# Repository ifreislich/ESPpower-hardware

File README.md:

# ESPpower-hardware

Hardware for reading EKM Omnimeters.

The barrel jack is center positive.

The RJ-12 connection
Pin|Signal
---|------
1|GND
2|RS485-B
3|RS485-A
4|GND
5|n.c.
6|n.c.

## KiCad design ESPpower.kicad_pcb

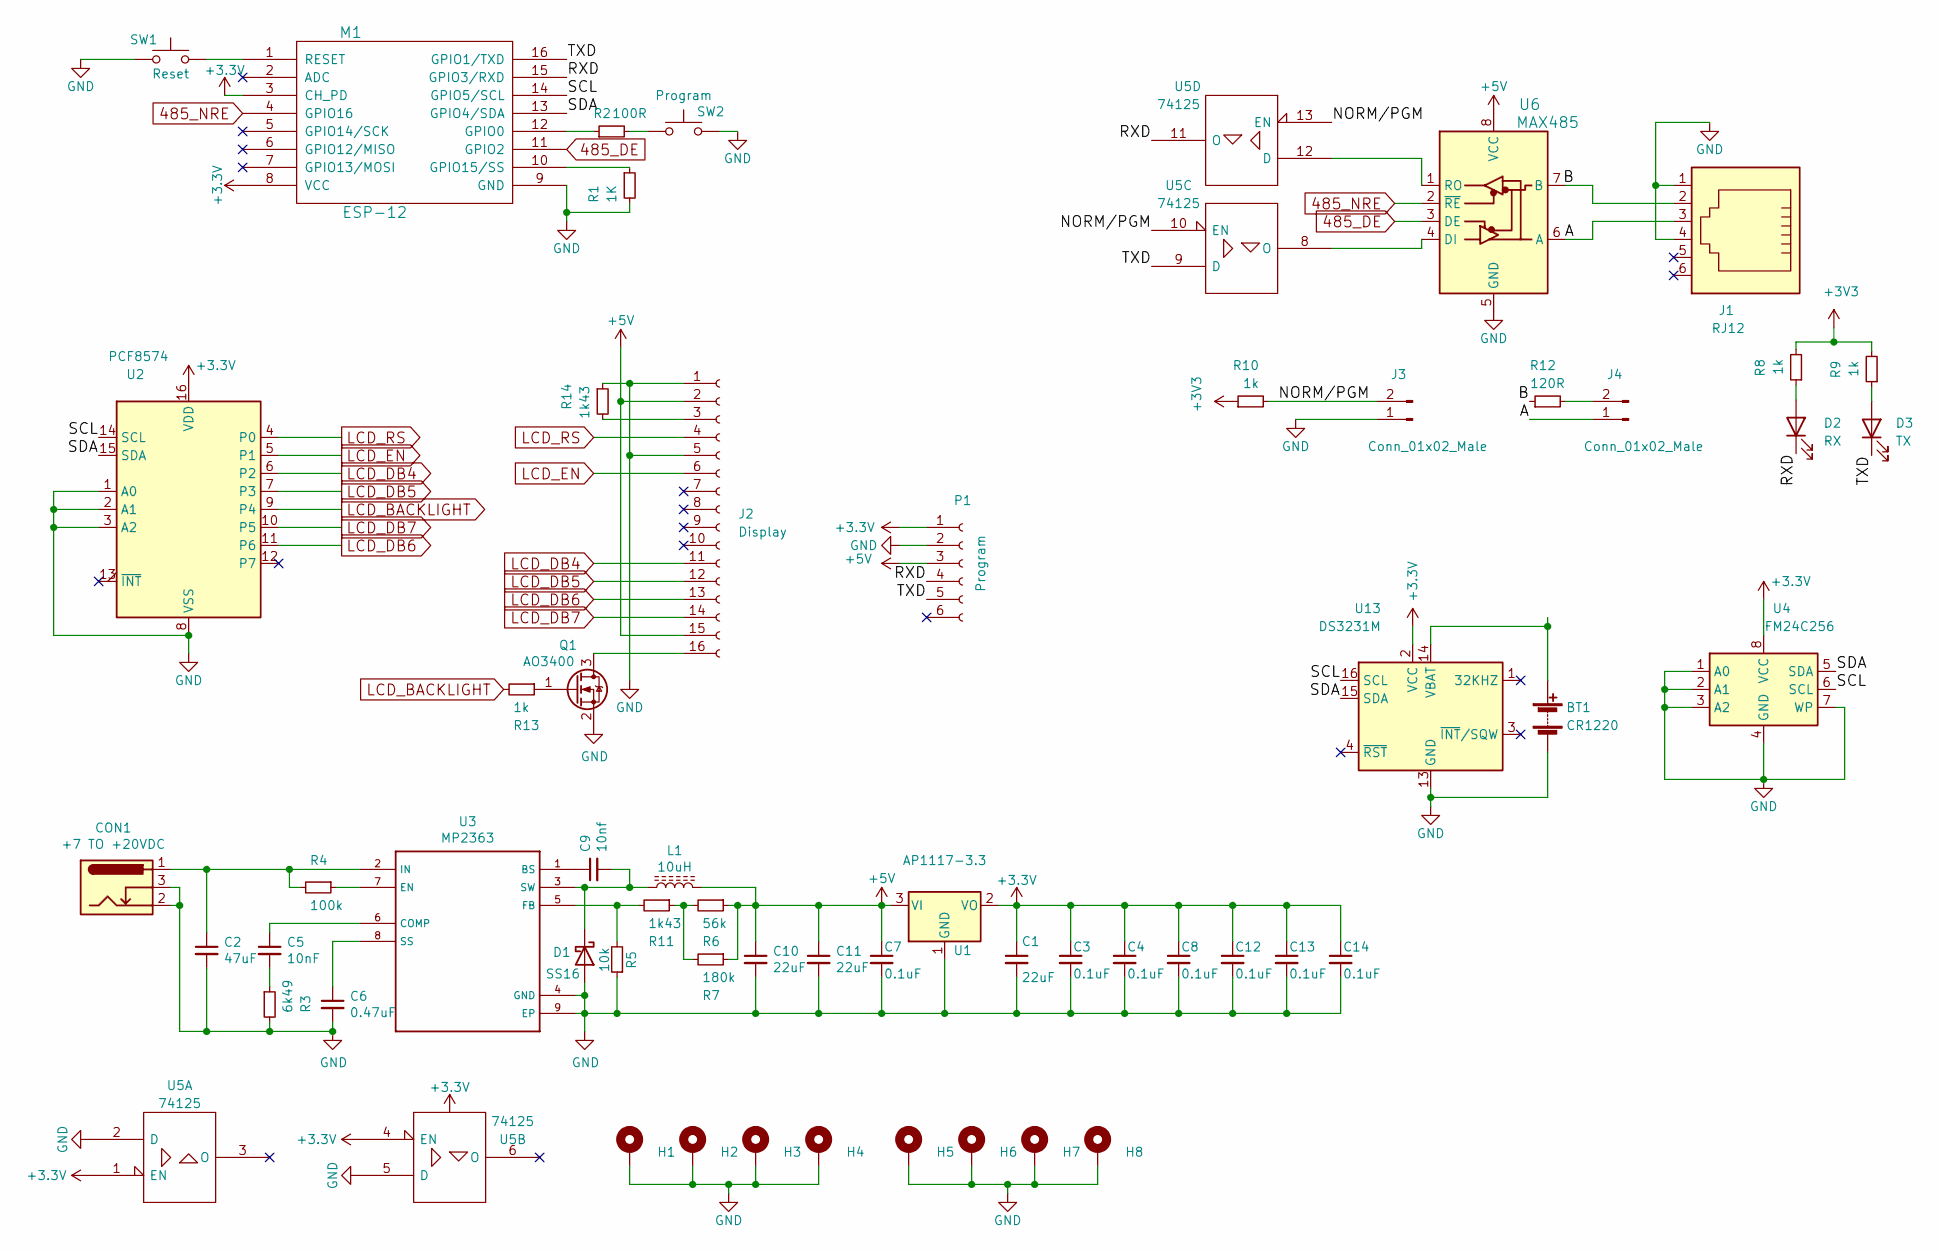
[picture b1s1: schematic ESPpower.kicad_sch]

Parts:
BT1: CR1220; CR1220SMD
C1: 22uF; C_1206_3216Metric
C2: 47uF; C_1206_3216Metric
C3, C4, C7, C8, C12, C13, C14: 0.1uF; C_0603_1608Metric
C5: 10nF; C_0805_2012Metric
C6: 0.47uF; C_0805_2012Metric
C9: 10nf; C_0805_2012Metric
C10, C11: 22uF; C_0805_2012Metric
CON1: +7 TO +20VDC; BarrelJack_Horizontal
D1: SS16; D_SMA
D2: RX; LED_0603_1608Metric
D3: TX; LED_0603_1608Metric
H1, H2, H3, H4, H5, H6, H7, H8: MountingHole_Pad; MountingHole_2.5mm_Pad_Via
J1: RJ12; RJ12_Amphenol_54601
J2: Display; PinSocket_1x16_P2.54mm_Vertical
J3, J4: Conn_01x02_Male; PinHeader_1x02_P2.54mm_Vertical
L1: 10uH; L_7.3x7.3_H3.5
M1: ESP-12; ESP-07
P1: Program; Pin_Header_Straight_1x06
Q1: AO3400; SOT-23
R1: 1K; R_0603_1608Metric
R2: 100R; R_0603_1608Metric
R3: 6k49; R_0603_1608Metric
R4: 100k; R_0603_1608Metric
R5: 10k; R_0603_1608Metric
R6: 56k; R_0805_2012Metric
R7: 180k; R_0805_2012Metric
R8, R9, R10, R13: 1k; R_0603_1608Metric
R11: 1k43; R_0805_2012Metric
R12: 120R; R_1206_3216Metric
R14: 1k43; R_0603_1608Metric
SW1: Reset; SW_PUSH_6mm
SW2: Program; SW_PUSH_6mm
U1: AP1117-3.3; SOT-223-3_TabPin2
U2: PCF8574; SOIC-16W_7.5x10.3mm_P1.27mm
U3: MP2363; HSOP-8-1EP_3.9x4.9mm_P1.27mm_EP2.41x3.1mm_ThermalVias
U4: FM24C256; SOIC-8_5.23x5.23mm_P1.27mm
U5: 74125; SOIC-14_3.9x8.7mm_P1.27mm
U6: MAX485; SOIC-8_3.9x4.9mm_P1.27mm
U13: DS3231M; SOIC-16W_7.5x10.3mm_P1.27mm

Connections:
485_DE: M1.11 (GPIO2), U6.3 (DE)
485_NRE: M1.4 (GPIO16), U6.2 (~RE)
+5V: C7.1, C10.1, C11.1, J2.2, J2.15, L1.2, P1.3, R6.1, R7.1, U1.3 (VI), U6.8 (VCC)
/A: J1.3, J4.1, U6.6 (A)
/B: J1.2, R12.1, U6.7 (B)
/NORM/PGM: J3.2, R10.2, U5.10 (EN), U5.13 (EN)
/RXD: D2.1 (K), M1.15 (GPIO3/RXD), P1.4, U5.11 (O)
/SCL: M1.14 (GPIO5/SCL), U2.14 (SCL), U4.6 (SCL), U13.16 (SCL)
/SDA: M1.13 (GPIO4/SDA), U2.15 (SDA), U4.5 (SDA), U13.15 (SDA)
/TXD: D3.1 (K), M1.16 (GPIO1/TXD), P1.5, U5.9 (D)
GND: BT1.2 (-), C1.2, C2.2, C3.2, C4.2, C6.2, C7.2, C8.2, C10.2, C11.2, C12.2, C13.2, C14.2, CON1.2, CON1.3, D1.2 (A), H1.1, H2.1, H3.1, H4.1, H5.1, H6.1, H7.1, H8.1, J1.1, J1.4, J2.1, J2.5, J3.1, M1.9 (GND), P1.2, Q1.2 (S), R1.2, R3.2, R5.1, R14.1, SW1.2, SW2.2, U1.1 (GND), U2.1 (A0), U2.2 (A1), U2.3 (A2), U2.8 (VSS), U3.4 (GND), U3.9 (EP), U4.1 (A0), U4.2 (A1), U4.3 (A2), U4.4 (GND), U4.7 (WP), U5.2 (D), U5.5 (D), U5.7 (GND), U6.5 (GND), U13.5 (GND), U13.6 (GND), U13.7 (GND), U13.8 (GND), U13.9 (GND), U13.10 (GND), U13.11 (GND), U13.12 (GND), U13.13 (GND)
LCD_BACKLIGHT: R13.2, U2.9 (P4)
LCD_DB4: J2.11, U2.6 (P2)
LCD_DB5: J2.12, U2.7 (P3)
LCD_DB6: J2.13, U2.11 (P6)
LCD_DB7: J2.14, U2.10 (P5)
LCD_EN: J2.6, U2.5 (P1)
LCD_RS: J2.4, U2.4 (P0)
unnamed: BT1.1 (+), U13.14 (VBAT)
unnamed: C2.1, CON1.1, R4.2, U3.2 (IN)
unnamed: C5.1, U3.6 (COMP)
unnamed: C5.2, R3.1
unnamed: C6.1, U3.8 (SS)
unnamed: C9.1, U3.1 (BS)
unnamed: C9.2, D1.1 (K), L1.1, U3.3 (SW)
unnamed: D2.2 (A), R8.1
unnamed: D3.2 (A), R9.1
unnamed: J2.3, R14.2
unnamed: J2.16, Q1.3 (D)
unnamed: J4.2, R12.2
unnamed: M1.1 (RESET), SW1.1
unnamed: M1.10 (GPIO15/SS), R1.1
unnamed: M1.12 (GPIO0), R2.1
unnamed: Q1.1 (G), R13.1
unnamed: R2.2, SW2.1
unnamed: R4.1, U3.7 (EN)
unnamed: R6.2, R7.2, R11.1
unnamed: R5.2, R11.2, U3.5 (FB)
unnamed: U5.8 (O), U6.4 (DI)
unnamed: U5.12 (D), U6.1 (RO)

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
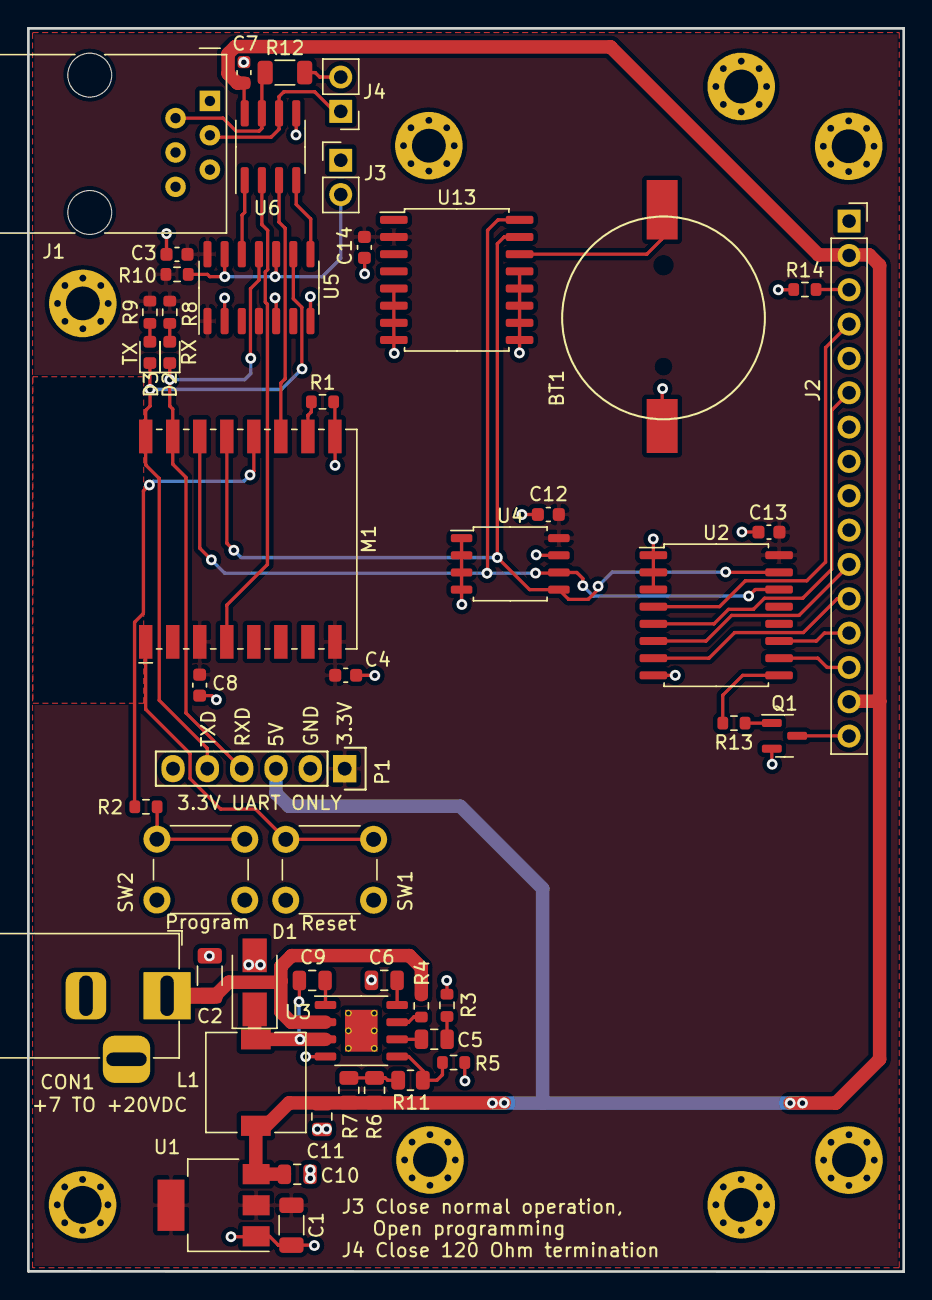
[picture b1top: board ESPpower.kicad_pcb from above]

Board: 2 copper layers, 64.8 x 92.0 mm, 58 parts (0 on the bottom side), 41 nets.

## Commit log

2021-05-30 Initial commit.
2021-05-31 Ignore local caches and add an image of the 3D render for the README.md
2021-05-31 Fix U4 part number to FM24C256 Fix U1 part to AP1117-3.3
2022-10-09 Saved with later KiCAD version.
